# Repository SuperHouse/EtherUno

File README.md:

SuperHouse EtherUNO
===================

The EtherUNO is a 100% Arduino Compatible Board, based on the Arduino
UNO reference design, but with improvements and updates for ease of use,
cost, and getting started. It also includes on-board Ethernet with PoE
(Power-over-Ethernet) support and uses a USB-C socket.

Features:

 * LEDs visible on the edge
 * USB-C Connector
 * I2C MAC address ROM
 * Overlay guide where you need it (both top and bottom)
 * D13 pin works for everything
 * RX pin biased
 * Mounting holes

More information is available at:

  https://www.superhouse.tv/eu

Hardware
--------
The "Hardware" directory contains the PCB design as an EAGLE project.
EAGLE PCB design software is available from Autodesk free for
non-commercial use.

Credits
-------
 * Jonathan Oxer <jon@oxer.com.au>

 The EtherUNO is based on the EtherTen, which was designed by Jonathan
 Oxer and Marc Alexander.

License
-------
Copyright 2020 SuperHouse Automation Pty Ltd  www.superhouse.tv  

The hardware portion of this project is licensed under the TAPR Open
Hardware License (www.tapr.org/OHL). The "license" folder within this
repository contains a copy of this license in plain text format.

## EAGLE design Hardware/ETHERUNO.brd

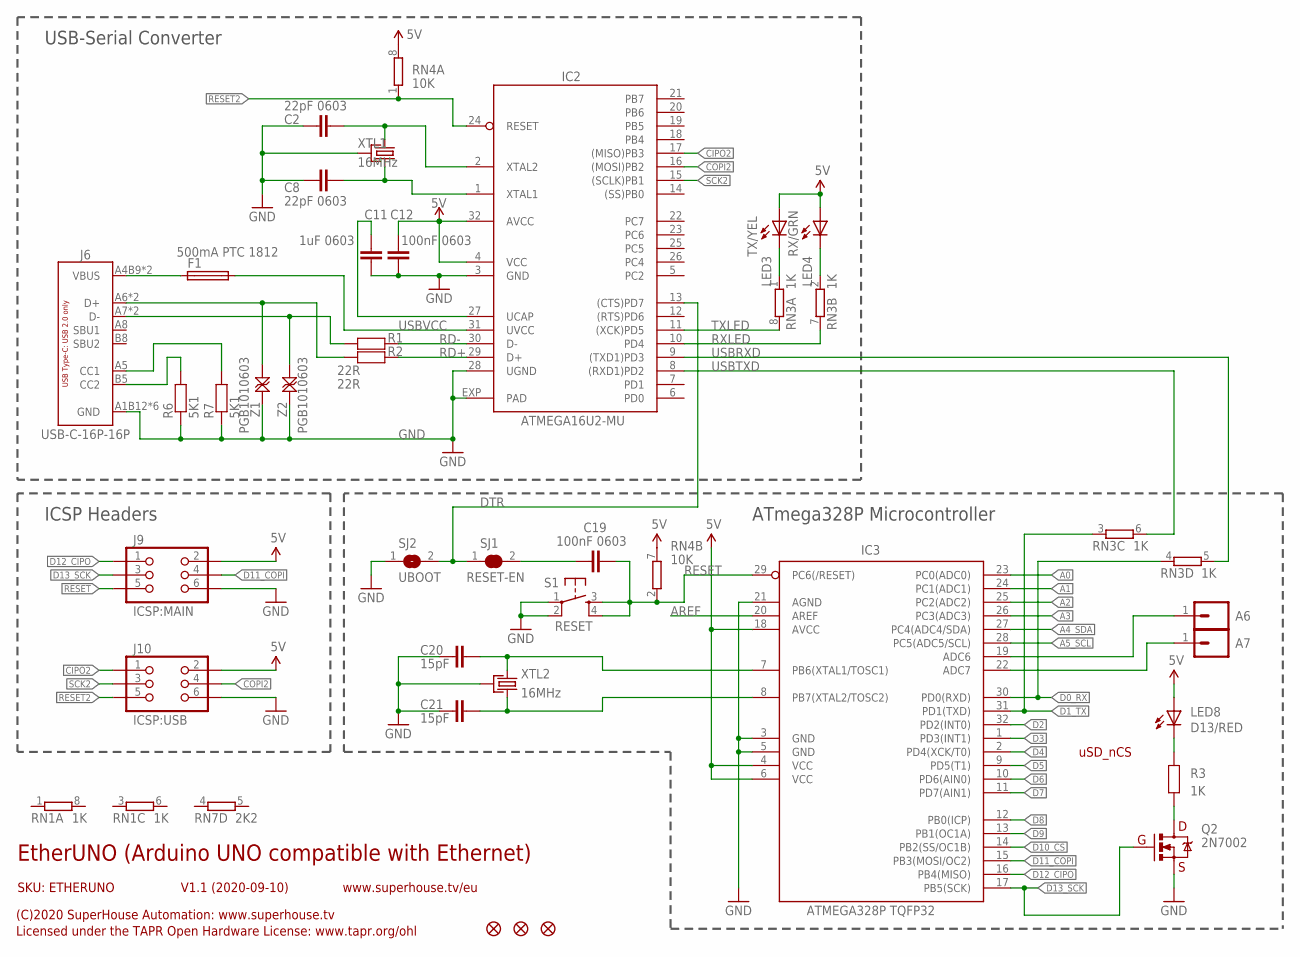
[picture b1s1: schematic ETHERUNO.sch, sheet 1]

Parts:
A6: A6; 1X01
A7: A7; 1X01
C2, C8: 22pF 0603; C0603
C11: 1uF 0603; C0603
C12, C19: 100nF 0603; C0603
C20, C21: 15pF; C0603
F1: 500mA PTC 1812; 1812
FID1, FID2, FID3: FIDUCIAL1X2.5; FIDUCIAL-1X2.5
IC2: ATMEGA16U2-MU; ATMEL_QFN32
IC3: ATMEGA328P TQFP32; TQFP32-08
J6: USB-C-16P-16P; USB-C-16P
J9: ICSP:MAIN; 2X03-ICSP
J10: ICSP:USB; 2X03-ICSP
LED3: TX/YEL; LED-0603
LED4: RX/GRN; LED-0603
LED8: D13/RED; LED-0603
Q2: 2N7002; SOT23-3
R1, R2: 22R; R0603
R3: 1K; R0603
R6, R7: 5K1; R0603
RN1, RN3: 1K; CAY16
RN4: 10K; CAY16
RN7: 2K2; CAY16
S1: RESET; TACTILE_SMT-6MM
SJ1: RESET-EN; SJC
SJ2: UBOOT; SJ
XTL1, XTL2: 16MHz; CRYSTAL-SMD-3X2
Z1, Z2: PGB1010603; TVS0603

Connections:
5V: C12.1, IC2.4 (VCC), IC2.32 (AVCC), IC3.4 (VCC), IC3.6 (VCC), IC3.18 (AVCC), J9.2, J10.2, LED3.A, LED4.A, LED8.A, RN4.7 (2), RN4.8 (2); also elsewhere on the board
A0: IC3.23 (PC0(ADC0)); also elsewhere on the board
A1: IC3.24 (PC1(ADC1)); also elsewhere on the board
A2: IC3.25 (PC2(ADC2)); also elsewhere on the board
A3: IC3.26 (PC3(ADC3)); also elsewhere on the board
A4_SDA: IC3.27 (PC4(ADC4/SDA)); also elsewhere on the board
A5_SCL: IC3.28 (PC5(ADC5/SCL)); also elsewhere on the board
AREF: IC3.20 (AREF); also elsewhere on the board
CIPO2: IC2.17 ((MISO)PB3), J10.1
COPI2: IC2.16 ((MOSI)PB2), J10.4
D0_RX: IC3.30 (PD0(RXD)), RN3.4 (1); also elsewhere on the board
D1_TX: IC3.31 (PD1(TXD)), RN3.3 (1); also elsewhere on the board
D2: IC3.32 (PD2(INT0)); also elsewhere on the board
D3: IC3.1 (PD3(INT1)); also elsewhere on the board
D4: IC3.2 (PD4(XCK/T0)); also elsewhere on the board
D5: IC3.9 (PD5(T1)); also elsewhere on the board
D6: IC3.10 (PD6(AIN0)); also elsewhere on the board
D7: IC3.11 (PD7(AIN1)); also elsewhere on the board
D8: IC3.12 (PB0(ICP)); also elsewhere on the board
D9: IC3.13 (PB1(OC1A)); also elsewhere on the board
D10_CS: IC3.14 (PB2(SS/OC1B)); also elsewhere on the board
D11_COPI: IC3.15 (PB3(MOSI/OC2)), J9.4; also elsewhere on the board
D12_CIPO: IC3.16 (PB4(MISO)), J9.1; also elsewhere on the board
D13_SCK: IC3.17 (PB5(SCK)), J9.3, Q2.1 (G); also elsewhere on the board
DTR: IC2.13 ((CTS)PD7), SJ1.1, SJ2.2
GND: C2.1, C8.1, C11.2, C12.2, C20.1, C21.1, IC2.3 (GND), IC2.28 (UGND), IC2.EXP (PAD), IC3.3 (GND), IC3.5 (GND), IC3.21 (AGND), J6.A1B12 (GND), J6.A12B1 (GND), J6.FIX1 (GND), J6.FIX2 (GND), J6.FIX3 (GND), J6.FIX4 (GND), J9.6, J10.6, Q2.2 (S), R6.1, R7.1, S1.1, S1.2, SJ2.1, XTL1.2 (GND), XTL1.4 (GND), XTL2.2 (GND), XTL2.4 (GND), Z1.2, Z2.2; also elsewhere on the board
unnamed: C20.2, IC3.7 (PB6(XTAL1/TOSC1)), XTL2.1
unnamed: C19.1, SJ1.2
unnamed: LED8.C, R3.2
unnamed: Q2.3 (D), R3.1
unnamed: C21.2, IC3.8 (PB7(XTAL2/TOSC2)), XTL2.3 (2)
unnamed: C8.2, IC2.1 (XTAL1), XTL1.3 (2)
unnamed: J6.B5 (CC2), R6.2
unnamed: LED4.C, RN3.2 (1)
unnamed: LED3.C, RN3.1
unnamed: J6.A6 (D+), J6.B6 (D+), R2.2, Z1.1
unnamed: J6.A7 (D-), J6.B7 (D-), R1.2, Z2.1
unnamed: A7.1, IC3.22 (ADC7)
unnamed: A6.1, IC3.19 (ADC6)
unnamed: J6.A5 (CC1), R7.2
unnamed: C2.2, IC2.2 (XTAL2), XTL1.1
unnamed: F1.1, J6.A4B9 (VBUS), J6.A9B4 (VBUS)
unnamed: C11.1, IC2.27 (UCAP)
RD+: IC2.29 (D+), R2.1
RD-: IC2.30 (D-), R1.1
RESET: C19.2, IC3.29 (PC6(/RESET)), J9.5, RN4.2 (1), S1.3, S1.4; also elsewhere on the board
RESET2: IC2.24 (RESET), J10.5, RN4.1
RXLED: IC2.10 (PD4), RN3.7 (2)
SCK2: IC2.15 ((SCLK)PB1), J10.3
TXLED: IC2.11 ((XCK)PD5), RN3.8 (2)
USBRXD: IC2.9 ((TXD1)PD3), RN3.5 (2)
USBTXD: IC2.8 ((RXD1)PD2), RN3.6 (2)
USBVCC: F1.2, IC2.31 (UVCC); also elsewhere on the board

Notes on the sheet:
uSD_nCS
EtherUNO (Arduino UNO compatible with Ethernet)
SKU: ETHERUNO
(C)2020 SuperHouse Automation: www.superhouse.tv
Licensed under the TAPR Open Hardware License: www.tapr.org/ohl
www.superhouse.tv/eu
V1.1 (2020-09-10)
ICSP Headers
USB-Serial Converter
ATmega328P Microcontroller

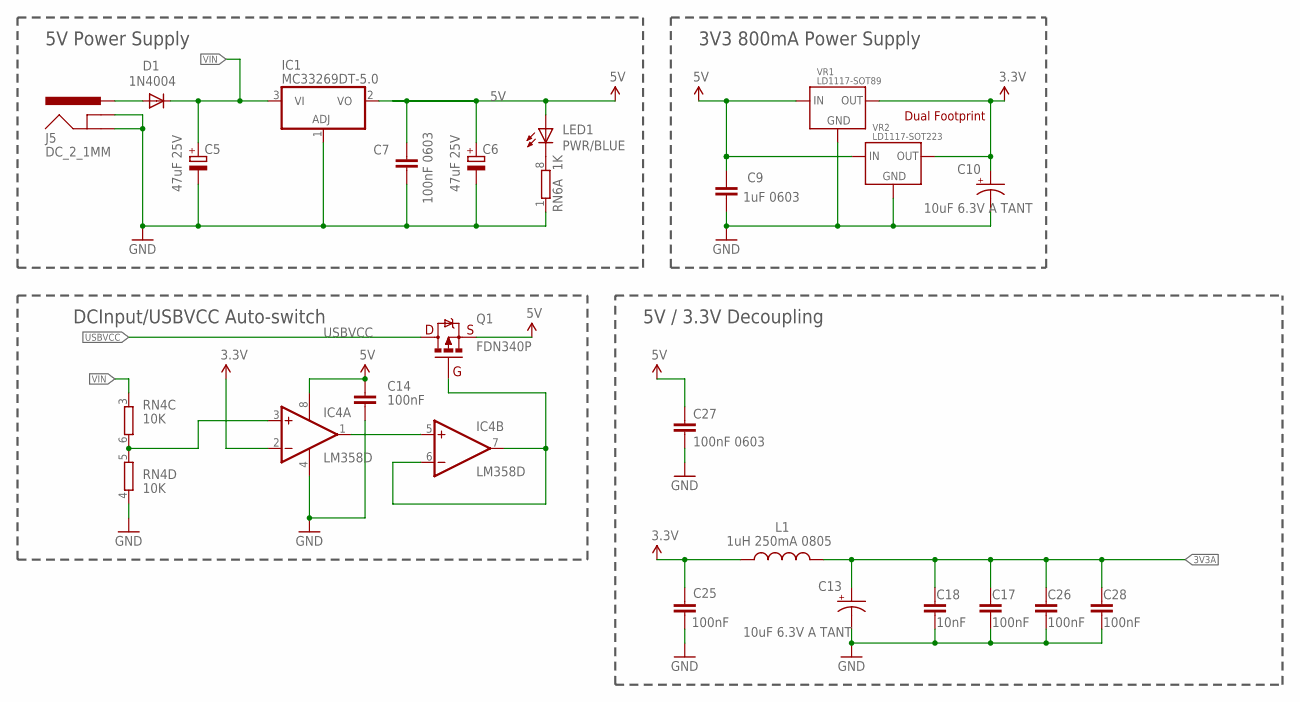
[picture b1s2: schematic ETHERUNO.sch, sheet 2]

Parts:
C5, C6: 47uF 25V; PANASONIC_D
C7, C27: 100nF 0603; C0603
C9: 1uF 0603; C0603
C10, C13: 10uF 6.3V A TANT; EIA3216
C14, C17, C25, C26, C28: 100nF; C0603
C18: 10nF; C0603
D1: 1N4004; SMA-DIODE
IC1: MC33269DT-5.0; DPACK
IC4: LM358D; SO08
J5: DC_2_1MM; POWER_JACK_SLOTS
L1: 1uH 250mA 0805; L2012C
LED1: PWR/BLUE; LED-0603
Q1: FDN340P; SOT23
RN4: 10K; CAY16
RN6: 1K; CAY16
VR1: LD1117-SOT89; SOT89
VR2: LD1117-SOT223; SOT-223

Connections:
3.3V: C10.A (+), C25.1, IC4.2 (-IN), L1.1, VR1.2 (OUT), VR1.4 (OUT), VR2.2 (OUT), VR2.4 (OUT); also elsewhere on the board
3V3A: C13.A (+), C17.1, C18.1, C26.1, C28.1, L1.2; also elsewhere on the board
5V: C6.+, C7.1, C9.1, C14.1, C27.1, IC1.2 (VO), IC4.8 (V+), LED1.A, Q1.2 (S), VR1.3 (IN), VR2.3 (IN); also elsewhere on the board
GND: C5.-, C6.-, C7.2, C9.2, C10.C (-), C13.C (-), C14.2, C17.2, C18.2, C25.2, C26.2, C27.2, C28.2, IC1.1 (ADJ), IC4.4 (V-), J5.GND, J5.GNDBREAK, RN4.4 (1), RN6.1, VR1.1 (GND), VR2.1 (GND); also elsewhere on the board
unnamed: IC4.3 (+IN), RN4.5 (2), RN4.6 (2)
unnamed: LED1.C, RN6.8 (2)
unnamed: IC4.6 (-IN), IC4.7 (OUT), Q1.1 (G)
unnamed: IC4.1 (OUT), IC4.5 (+IN)
unnamed: D1.A, J5.PWR
USBVCC: Q1.3 (D); also elsewhere on the board
VIN: C5.+, D1.C, IC1.3 (VI), RN4.3 (1); also elsewhere on the board

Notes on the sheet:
3V3 800mA Power Supply
Dual Footprint
5V Power Supply
DCInput/USBVCC Auto-switch
5V / 3.3V Decoupling

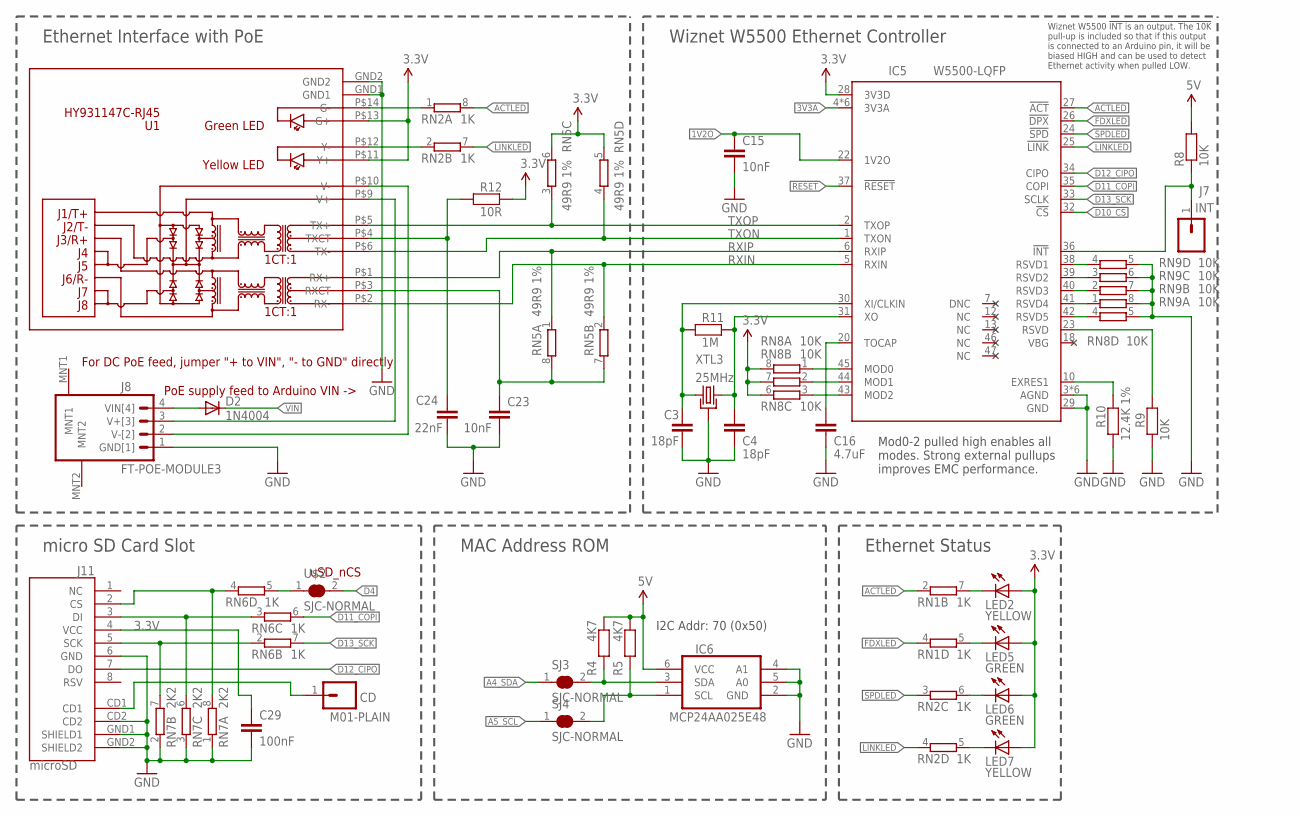
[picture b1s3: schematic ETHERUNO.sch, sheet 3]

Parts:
C3, C4: 18pF; C0603
C15, C23: 10nF; C0603
C16: 4.7uF; C0603
C24: 22nF; C0603
C29: 100nF; C0603
CD: M01-PLAIN; 1X01
D2: 1N4004; SMA-DIODE
IC5: W5500-LQFP; LQFP48
IC6: MCP24AA025E48; SOT23-6
J7: INT; 1X01
J8: FT-POE-MODULE3; FT-POE-MODULE-NOLABEL
J11: microSD; MICRO-SD-SOCKET-PP
LED2, LED7: YELLOW; LED-0603
LED5, LED6: GREEN; LED-0603
R4, R5: 4K7; R0603
R8, R9: 10K; R0603
R10: 12.4K 1%; R0603
R11: 1M; R0603
R12: 10R; R0603
RN1, RN2, RN6: 1K; CAY16
RN5: 49R9 1%; CAY16
RN7: 2K2; CAY16
RN8, RN9: 10K; CAY16
SJ3, SJ4: SJC-NORMAL; SJC
U1: HY931147C-RJ45; HY931147C
U$2: SJC-NORMAL; SJC
XTL3: 25MHz; CRYSTAL-SMD-3X2

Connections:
1V2O: C15.1, IC5.22 (1V2O)
3.3V: C29.1, IC5.28 (3V3D), J11.4 (VCC), LED2.A, LED5.A, LED6.A, LED7.A, R12.1, RN5.5 (2), RN5.6 (2), RN8.6 (2), RN8.7 (2), RN8.8 (2), U1.P$11 (Y+), U1.P$13 (G+); also elsewhere on the board
3V3A: IC5.4 (3V3A), IC5.8 (3V3A), IC5.11 (3V3A), IC5.15 (3V3A), IC5.17 (3V3A), IC5.21 (3V3A); also elsewhere on the board
5V: IC6.6 (VCC), R4.1, R5.1, R8.2; also elsewhere on the board
A4_SDA: SJ3.1; also elsewhere on the board
A5_SCL: SJ4.1; also elsewhere on the board
ACTLED: IC5.27 (!ACT), RN1.2 (1), RN2.8 (2)
D4: U$2.2; also elsewhere on the board
D10_CS: IC5.32 (!CS); also elsewhere on the board
D11_COPI: IC5.35 (COPI), RN6.6 (2); also elsewhere on the board
D12_CIPO: IC5.34 (CIPO), J11.7 (DO); also elsewhere on the board
D13_SCK: IC5.33 (SCLK), RN6.7 (2); also elsewhere on the board
FDXLED: IC5.26 (!DPX), RN1.4 (1)
GND: C3.2, C4.2, C15.2, C16.2, C23.2, C24.2, C29.2, IC5.3 (AGND), IC5.9 (AGND), IC5.14 (AGND), IC5.16 (AGND), IC5.19 (AGND), IC5.29 (GND), IC5.48 (AGND), IC6.2 (GND), IC6.4 (A1), IC6.5 (A0), J8.1 (GND[1]), J11.6 (GND), J11.CD2, J11.GND1 (SHIELD1), J11.GND2 (SHIELD2), R9.2, R10.2, RN7.1, RN7.2 (1), RN7.3 (1), RN8.5 (2), RN9.5 (2), RN9.6 (2), RN9.7 (2), RN9.8 (2), U1.GND1, U1.GND2, XTL3.2 (GND), XTL3.4 (GND); also elsewhere on the board
LINKLED: IC5.25 (!LINK), RN2.4 (1), RN2.7 (2)
unnamed: C23.1, RN5.7 (2), RN5.8 (2), U1.P$3 (RXCT)
unnamed: IC6.1 (SCL), R5.2, SJ4.2
unnamed: C4.1, IC5.31 (XO), R11.1, XTL3.3 (2)
unnamed: D2.A, J8.4 (VIN[4])
unnamed: J11.2 (CS), RN6.4 (1), RN7.8 (2)
unnamed: CD.1, J11.CD1
unnamed: J11.5 (SCK), RN6.2 (1), RN7.7 (2)
unnamed: J11.3 (DI), RN6.3 (1), RN7.6 (2)
unnamed: LED6.C, RN2.6 (2)
unnamed: C3.1, IC5.30 (XI/CLKIN), R11.2, XTL3.1
unnamed: LED7.C, RN2.5 (2)
unnamed: IC6.3 (SDA), R4.2, SJ3.2
unnamed: C16.1, IC5.20 (TOCAP)
unnamed: C24.1, R12.2, U1.P$4 (TXCT)
unnamed: IC5.10 (EXRES1), R10.1
unnamed: IC5.23 (RSVD), R9.1
unnamed: IC5.36 (!INT), J7.1, R8.1
unnamed: IC5.45 (MOD0), RN8.1
unnamed: IC5.44 (MOD1), RN8.2 (1)
unnamed: IC5.43 (MOD2), RN8.3 (1)
unnamed: IC5.42 (RSVD5), RN8.4 (1)
unnamed: IC5.41 (RSVD4), RN9.1
unnamed: IC5.40 (RSVD3), RN9.2 (1)
unnamed: IC5.39 (RSVD2), RN9.3 (1)
unnamed: IC5.38 (RSVD1), RN9.4 (1)
unnamed: RN6.5 (2), U$2.1
unnamed: RN2.1, U1.P$14 (G-)
unnamed: J8.3 (V+[3]), U1.P$9 (V+)
unnamed: J8.2 (V-[2]), U1.P$10 (V-)
unnamed: LED5.C, RN1.5 (2)
unnamed: LED2.C, RN1.7 (2)
unnamed: RN2.2 (1), U1.P$12 (Y-)
RESET: IC5.37 (!RESET); also elsewhere on the board
RXIN: IC5.5 (RXIN), RN5.2 (1), U1.P$2 (RX-)
RXIP: IC5.6 (RXIP), RN5.1, U1.P$1 (RX+)
SPDLED: IC5.24 (!SPD), RN2.3 (1)
TXON: IC5.1 (TXON), RN5.4 (1), U1.P$6 (TX-)
TXOP: IC5.2 (TXOP), RN5.3 (1), U1.P$5 (TX+)
VIN: D2.C; also elsewhere on the board

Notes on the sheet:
uSD_nCS
micro SD Card Slot
I2C Addr: 70 (0x50)
Ethernet Status
PoE supply feed to Arduino VIN ->
For DC PoE feed, jumper "+ to VIN", "- to GND" directly
Ethernet Interface with PoE
MAC Address ROM
Wiznet W5500 Ethernet Controller
Mod0-2 pulled high enables all modes. Strong external pullups improves EMC performance.
Wiznet W5500 !INT is an output. The 10K pull-up is included so that if this output is connected to an Arduino pin, it will be biased HIGH and can be used to detect Ethernet activity when pulled LOW.

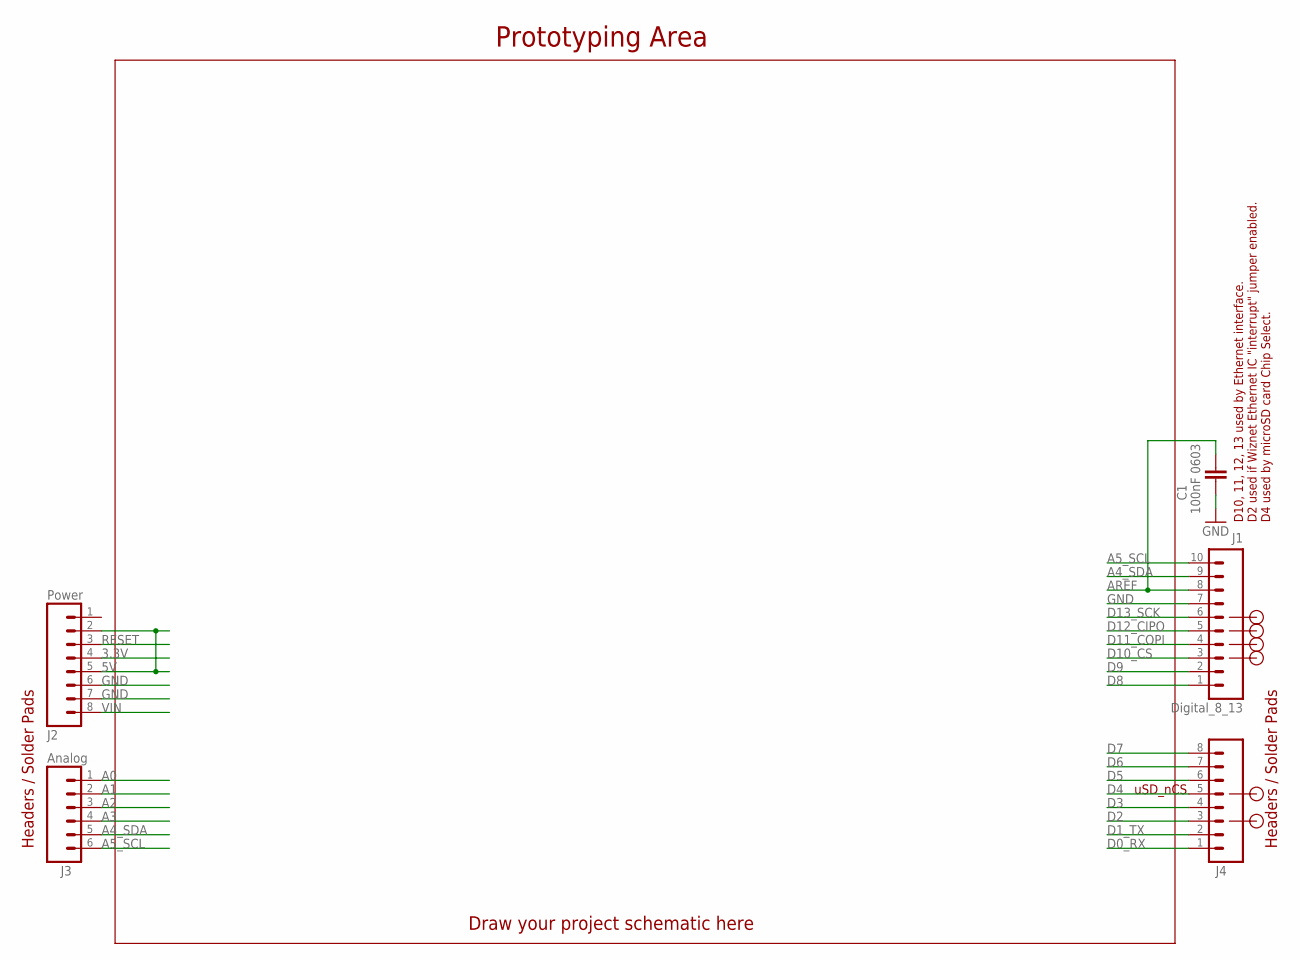
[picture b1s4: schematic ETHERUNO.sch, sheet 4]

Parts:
C1: 100nF 0603; C0603
J1: Digital_8_13; 1X10-S
J2: Power; 1X08-S
J3: Analog; 1X06-S
J4: Digital_0_7; 1X08-S

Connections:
3.3V: J2.4; also elsewhere on the board
5V: J2.2, J2.5; also elsewhere on the board
A0: J3.1; also elsewhere on the board
A1: J3.2; also elsewhere on the board
A2: J3.3; also elsewhere on the board
A3: J3.4; also elsewhere on the board
A4_SDA: J1.9, J3.5; also elsewhere on the board
A5_SCL: J1.10, J3.6; also elsewhere on the board
AREF: C1.1, J1.8; also elsewhere on the board
D0_RX: J4.1; also elsewhere on the board
D1_TX: J4.2; also elsewhere on the board
D2: J4.3; also elsewhere on the board
D3: J4.4; also elsewhere on the board
D4: J4.5; also elsewhere on the board
D5: J4.6; also elsewhere on the board
D6: J4.7; also elsewhere on the board
D7: J4.8; also elsewhere on the board
D8: J1.1; also elsewhere on the board
D9: J1.2; also elsewhere on the board
D10_CS: J1.3; also elsewhere on the board
D11_COPI: J1.4; also elsewhere on the board
D12_CIPO: J1.5; also elsewhere on the board
D13_SCK: J1.6; also elsewhere on the board
GND: C1.2, J1.7, J2.6, J2.7; also elsewhere on the board
RESET: J2.3; also elsewhere on the board
VIN: J2.8; also elsewhere on the board

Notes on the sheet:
Prototyping Area
Headers / Solder Pads
Draw your project schematic here
D10, 11, 12, 13 used by Ethernet interface.
D2 used if Wiznet Ethernet IC "interrupt" jumper enabled.
uSD_nCS
D4 used by microSD card Chip Select.

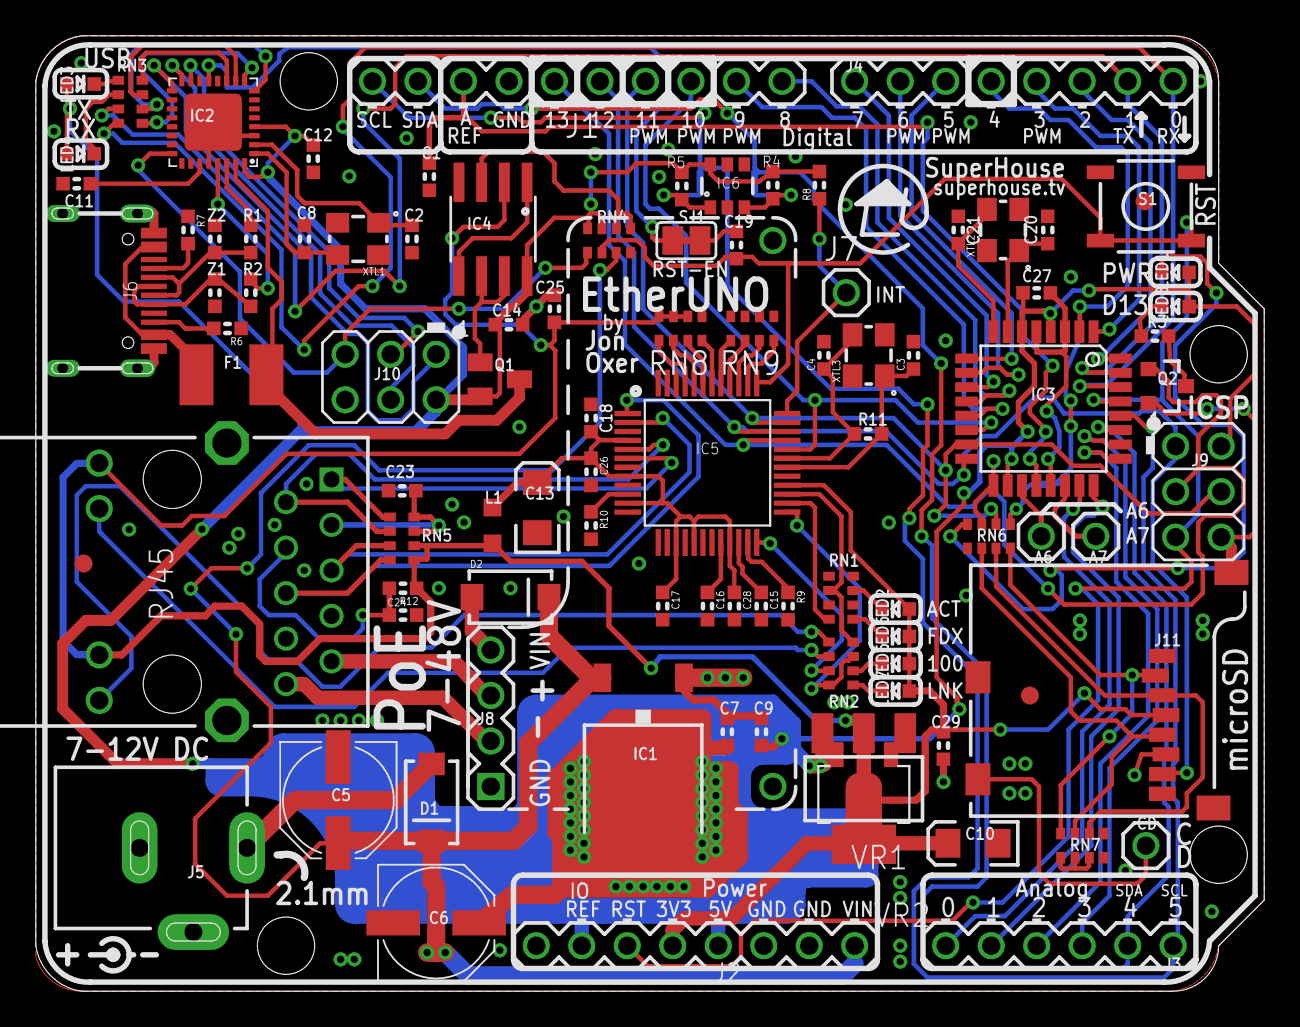
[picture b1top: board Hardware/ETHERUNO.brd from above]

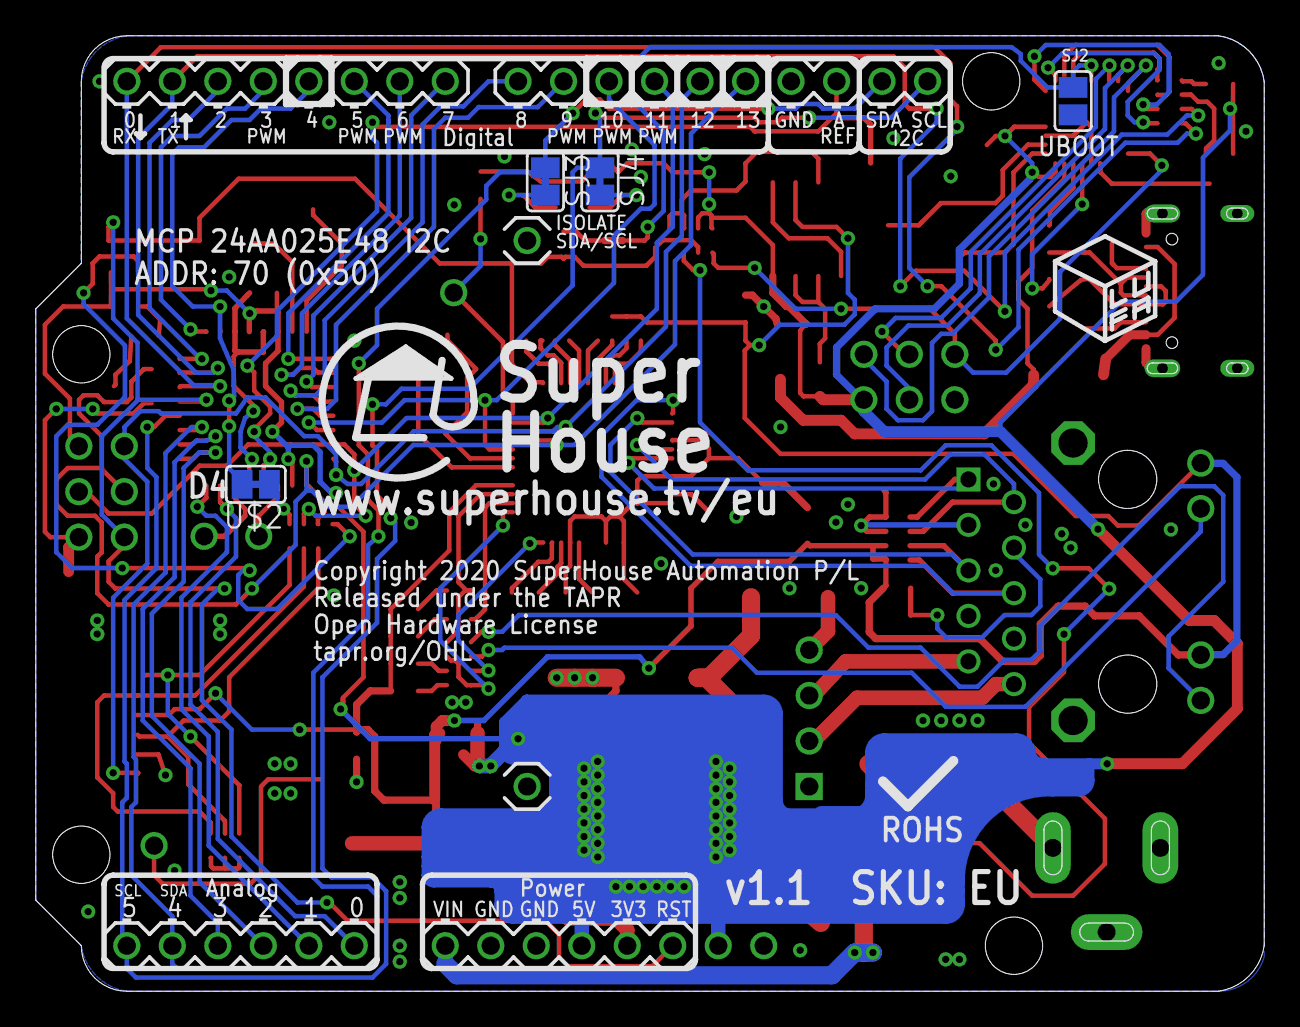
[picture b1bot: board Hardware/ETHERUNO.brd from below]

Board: 2 copper layers, 68.6 x 53.3 mm, 100 parts (4 on the bottom side), 102 nets.

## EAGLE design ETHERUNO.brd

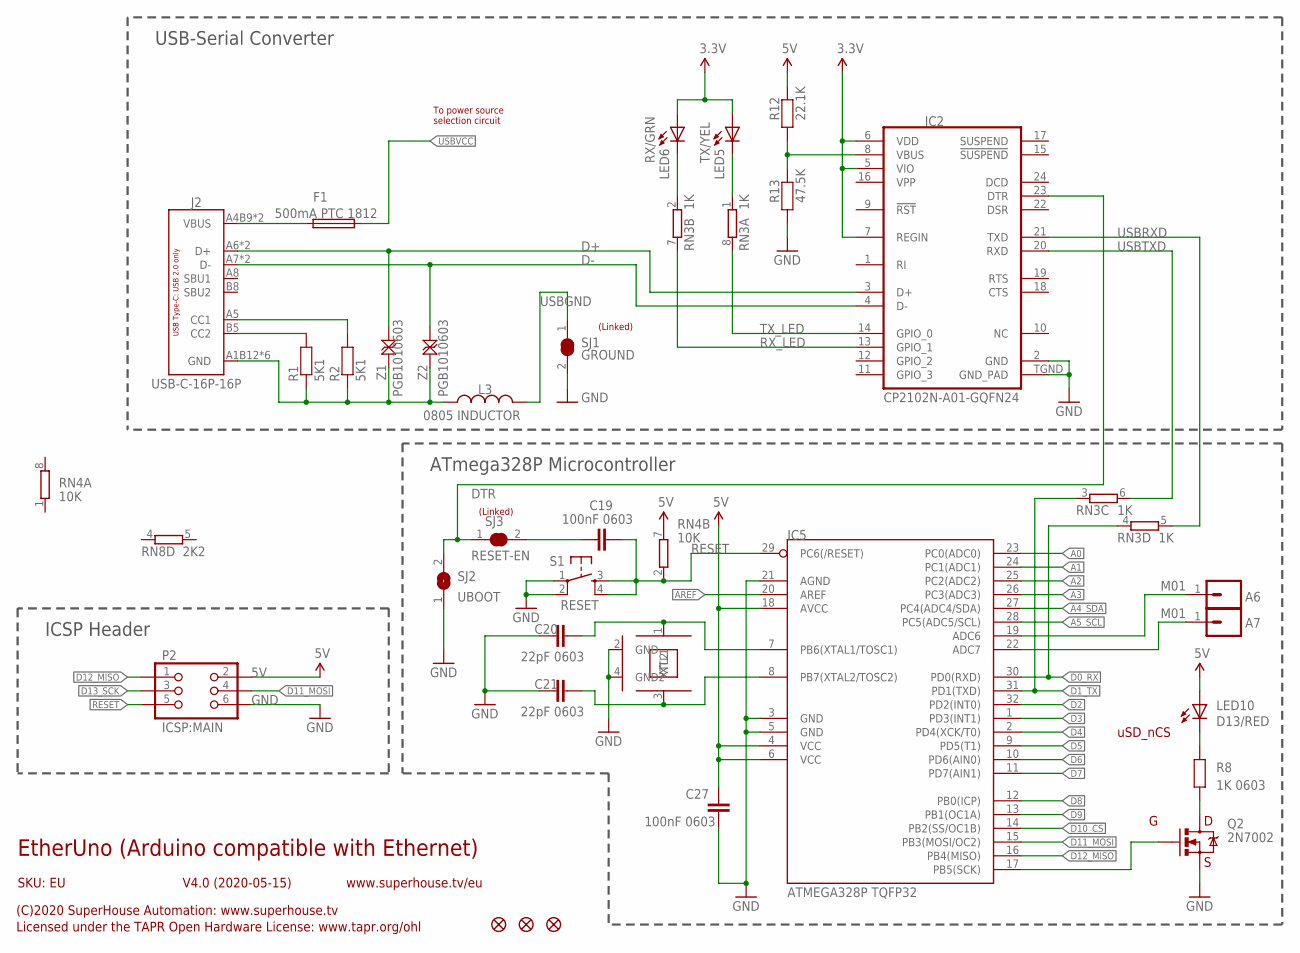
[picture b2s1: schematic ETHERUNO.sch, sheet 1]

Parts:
A6, A7: M01; 1X01
C19, C27: 100nF 0603; C0603
C20, C21: 22pF 0603; C0603
F1: 500mA PTC 1812; 1812
FID1, FID2, FID3: FIDUCIAL1X2.5; FIDUCIAL-1X2.5
IC2: CP2102N-A01-GQFN24; QFN-24
IC5: ATMEGA328P TQFP32; TQFP32-08
J2: USB-C-16P-16P; USB-C-16P
L3: 0805 INDUCTOR; 0805-LARGE
LED5: TX/YEL; LED-0603
LED6: RX/GRN; LED-0603
LED10: D13/RED; LED-0603
P2: ICSP:MAIN; 2X03-ICSP
Q2: 2N7002; SOT23-3
R1, R2: 5K1; R0603
R8: 1K 0603; R0603
R12: 22.1K; R0603
R13: 47.5K; R0603
RN3: 1K; CAY16
RN4: 10K; CAY16
RN8: 2K2; CAY16
S1: RESET; TACTILE_SMT-6MM
SJ1: GROUND; SJC
SJ2: UBOOT; SJ
SJ3: RESET-EN; SJC
U$19: CRYSTAL-GND3X2; CRYSTAL-SMD-3X2
Z1, Z2: PGB1010603; TVS0603

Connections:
3.3V: IC2.5 (VIO), IC2.6 (VDD), IC2.7 (REGIN), LED5.A, LED6.A; also elsewhere on the board
5V: C27.1, IC5.4 (VCC), IC5.6 (VCC), IC5.18 (AVCC), LED10.A, P2.2, R12.2, RN4.7 (2); also elsewhere on the board
A0: IC5.23 (PC0(ADC0)); also elsewhere on the board
A1: IC5.24 (PC1(ADC1)); also elsewhere on the board
A2: IC5.25 (PC2(ADC2)); also elsewhere on the board
A3: IC5.26 (PC3(ADC3)); also elsewhere on the board
A4_SDA: IC5.27 (PC4(ADC4/SDA)); also elsewhere on the board
A5_SCL: IC5.28 (PC5(ADC5/SCL)); also elsewhere on the board
AREF: IC5.20 (AREF); also elsewhere on the board
D0_RX: IC5.30 (PD0(RXD)), RN3.4 (1); also elsewhere on the board
D1_TX: IC5.31 (PD1(TXD)), RN3.3 (1); also elsewhere on the board
D2: IC5.32 (PD2(INT0)); also elsewhere on the board
D3: IC5.1 (PD3(INT1)); also elsewhere on the board
D4: IC5.2 (PD4(XCK/T0)); also elsewhere on the board
D5: IC5.9 (PD5(T1)); also elsewhere on the board
D6: IC5.10 (PD6(AIN0)); also elsewhere on the board
D7: IC5.11 (PD7(AIN1)); also elsewhere on the board
D8: IC5.12 (PB0(ICP)); also elsewhere on the board
D9: IC5.13 (PB1(OC1A)); also elsewhere on the board
D10_CS: IC5.14 (PB2(SS/OC1B)); also elsewhere on the board
D11_MOSI: IC5.15 (PB3(MOSI/OC2)), P2.4; also elsewhere on the board
D12_MISO: IC5.16 (PB4(MISO)), P2.1; also elsewhere on the board
D13_SCK: IC5.17 (PB5(SCK)), P2.3, Q2.1 (G); also elsewhere on the board
D+: IC2.3 (D+), J2.A6 (D+), J2.B6 (D+), Z1.1
D-: IC2.4 (D-), J2.A7 (D-), J2.B7 (D-), Z2.1
DTR: IC2.23 (DTR), SJ2.2, SJ3.1
GND: C20.1, C21.1, C27.2, IC2.2 (GND), IC2.TGND (GND_PAD), IC5.3 (GND), IC5.5 (GND), IC5.21 (AGND), P2.6, Q2.2 (S), R13.1, S1.1, S1.2, SJ1.2, SJ2.1, U$19.2 (GND), U$19.4 (GND2); also elsewhere on the board
unnamed: C20.2, IC5.7 (PB6(XTAL1/TOSC1)), U$19.1 (XTL1)
unnamed: C19.1, SJ3.2
unnamed: LED10.C, R8.2
unnamed: Q2.3 (D), R8.1
unnamed: C21.2, IC5.8 (PB7(XTAL2/TOSC2)), U$19.3 (XTL2)
unnamed: J2.A1B12 (GND), J2.A12B1 (GND), J2.FIX1 (GND), J2.FIX2 (GND), J2.FIX3 (GND), J2.FIX4 (GND), L3.1, R1.1, R2.1, Z1.2, Z2.2
unnamed: J2.B5 (CC2), R1.2
unnamed: LED6.C, RN3.2 (1)
unnamed: LED5.C, RN3.1
unnamed: A7.1, IC5.22 (ADC7)
unnamed: A6.1, IC5.19 (ADC6)
unnamed: J2.A5 (CC1), R2.2
unnamed: IC2.8 (VBUS), R12.1, R13.2
unnamed: F1.1, J2.A4B9 (VBUS), J2.A9B4 (VBUS)
RESET: C19.2, IC5.29 (PC6(/RESET)), P2.5, RN4.2 (1), S1.3, S1.4; also elsewhere on the board
RX_LED: IC2.13 (GPIO_1), RN3.7 (2)
TX_LED: IC2.14 (GPIO_0), RN3.8 (2)
USBGND: L3.2, SJ1.1
USBRXD: IC2.21 (TXD), RN3.5 (2)
USBTXD: IC2.20 (RXD), RN3.6 (2)
USBVCC: F1.2; also elsewhere on the board

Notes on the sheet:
uSD_nCS
(Linked)
EtherUno (Arduino compatible with Ethernet)
SKU: EU
(C)2020 SuperHouse Automation: www.superhouse.tv
Licensed under the TAPR Open Hardware License: www.tapr.org/ohl
www.superhouse.tv/eu
V4.0 (2020-05-15)
USB-Serial Converter
ATmega328P Microcontroller
ICSP Header
To power source selection circuit

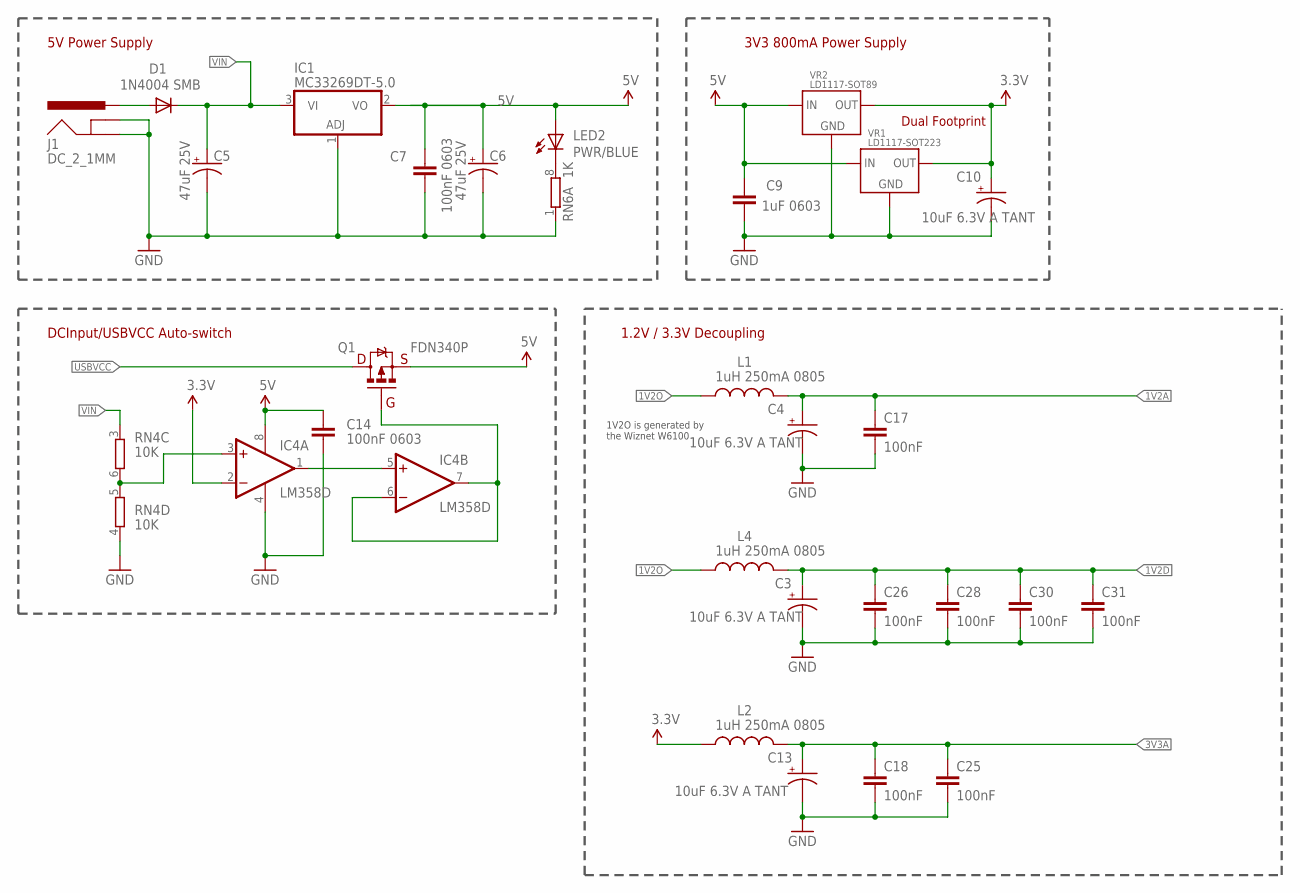
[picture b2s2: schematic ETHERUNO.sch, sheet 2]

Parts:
C3, C4, C10, C13: 10uF 6.3V A TANT; EIA3216
C5, C6: 47uF 25V; PANASONIC_D
C7, C14: 100nF 0603; C0603
C9: 1uF 0603; C0603
C17, C18, C25, C26, C28, C30, C31: 100nF; C0603
D1: 1N4004 SMB; SMA-DIODE
IC1: MC33269DT-5.0; DPACK
IC4: LM358D; SO08
J1: DC_2_1MM; POWER_JACK_SLOTS
L1, L2, L4: 1uH 250mA 0805; 0805-LARGE
LED2: PWR/BLUE; LED-0603
Q1: FDN340P; SOT23
RN4: 10K; CAY16
RN6: 1K; CAY16
VR1: LD1117-SOT223; SOT-223
VR2: LD1117-SOT89; SOT89

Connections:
1V2A: C4.A (+), C17.1, L1.2; also elsewhere on the board
1V2D: C3.A (+), C26.1, C28.1, C30.1, C31.1, L4.2; also elsewhere on the board
1V2O: L1.1, L4.1; also elsewhere on the board
3.3V: C10.A (+), IC4.2 (-IN), L2.1, VR1.2 (OUT), VR1.4 (OUT), VR2.2 (OUT), VR2.4 (OUT); also elsewhere on the board
3V3A: C13.A (+), C18.1, C25.1, L2.2; also elsewhere on the board
5V: C6.+, C7.1, C9.1, C14.1, IC1.2 (VO), IC4.8 (V+), LED2.A, Q1.2 (S), VR1.3 (IN), VR2.3 (IN); also elsewhere on the board
GND: C3.C (-), C4.C (-), C5.-, C6.-, C7.2, C9.2, C10.C (-), C13.C (-), C14.2, C17.2, C18.2, C25.2, C26.2, C28.2, C30.2, C31.2, IC1.1 (ADJ), IC4.4 (V-), J1.GND, J1.GNDBREAK, RN4.4 (1), RN6.1, VR1.1 (GND), VR2.1 (GND); also elsewhere on the board
unnamed: IC4.3 (+IN), RN4.5 (2), RN4.6 (2)
unnamed: LED2.C, RN6.8 (2)
unnamed: IC4.6 (-IN), IC4.7 (OUT), Q1.1 (G)
unnamed: IC4.1 (OUT), IC4.5 (+IN)
unnamed: D1.A, J1.PWR
USBVCC: Q1.3 (D); also elsewhere on the board
VIN: C5.+, D1.C, IC1.3 (VI), RN4.3 (1); also elsewhere on the board

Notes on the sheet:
5V Power Supply
DCInput/USBVCC Auto-switch
1.2V / 3.3V Decoupling
3V3 800mA Power Supply
Dual Footprint
1V2O is generated by the Wiznet W6100

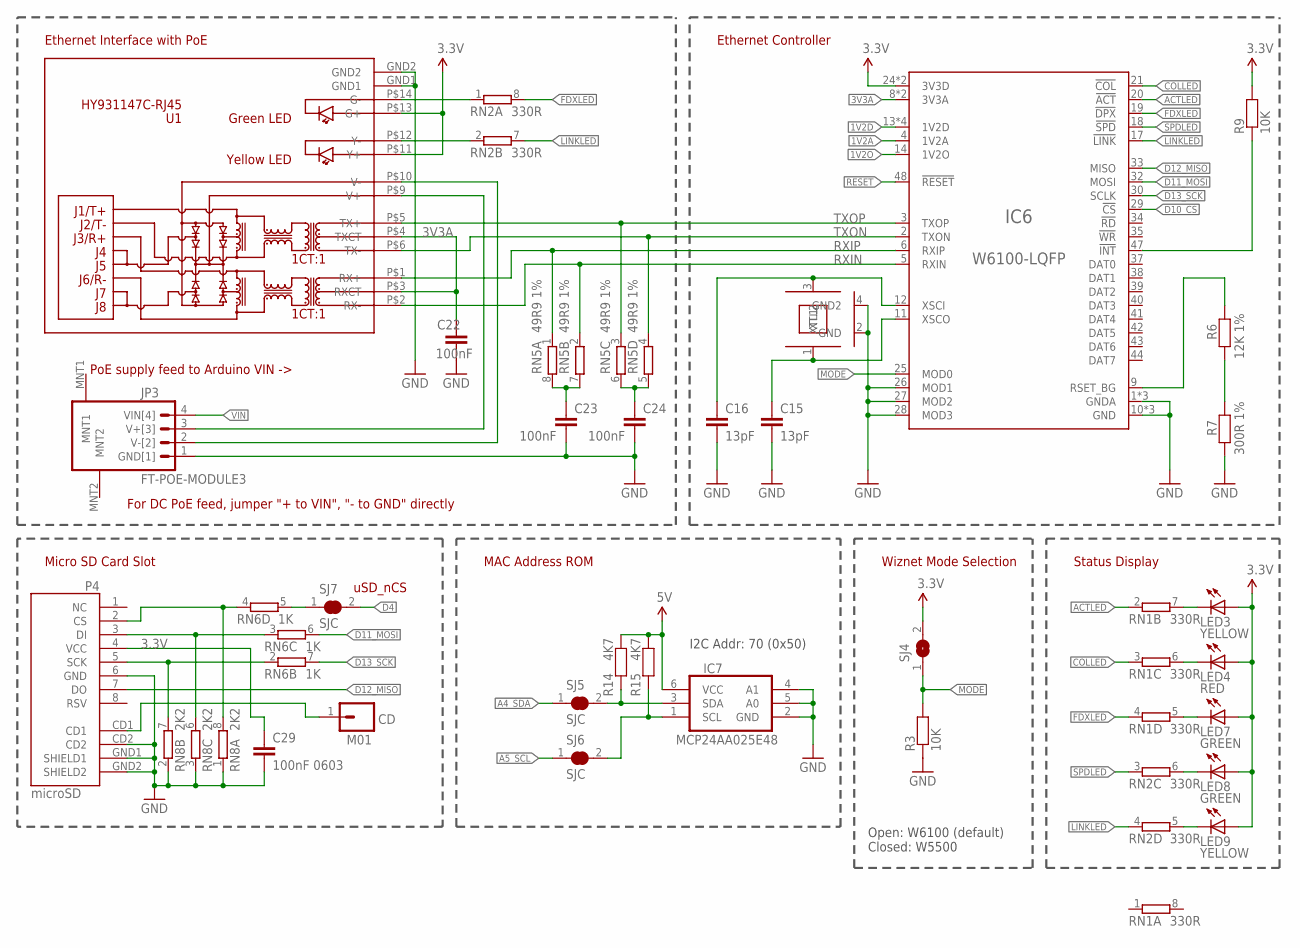
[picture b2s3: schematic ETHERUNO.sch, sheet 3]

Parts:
C15, C16: 13pF; C0603
C22, C23, C24: 100nF; C0603
C29: 100nF 0603; C0603
CD: M01; 1X01
IC6: W6100-LQFP; LQFP48
IC7: MCP24AA025E48; SOT23-6
JP3: FT-POE-MODULE3; FT-POE-MODULE-NOLABEL
LED3, LED9: YELLOW; LED-0603
LED4: RED; LED-0603
LED7, LED8: GREEN; LED-0603
P4: microSD; MICRO-SD-SOCKET-PP
R3, R9: 10K; R0603
R6: 12K 1%; R0603
R7: 300R 1%; R0603
R14, R15: 4K7; R0603
RN1, RN2: 330R; CAY16
RN5: 49R9 1%; CAY16
RN6: 1K; CAY16
RN8: 2K2; CAY16
SJ4: SJ-NORMAL; SJ
SJ5, SJ6, SJ7: SJC
U1: HY931147C-RJ45; HY931147C
U$17: CRYSTAL-GND3X2; CRYSTAL-SMD-3X2

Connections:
1V2A: IC6.4 (1V2A); also elsewhere on the board
1V2D: IC6.13 (1V2D), IC6.22 (1V2D), IC6.31 (1V2D), IC6.45 (1V2D); also elsewhere on the board
1V2O: IC6.14 (1V2O); also elsewhere on the board
3.3V: C29.1, IC6.24 (3V3D), IC6.36 (3V3D), LED3.A, LED4.A, LED7.A, LED8.A, LED9.A, P4.4 (VCC), R9.2, SJ4.2, U1.P$11 (Y+), U1.P$13 (G+); also elsewhere on the board
3V3A: C22.1, IC6.8 (3V3A), IC6.15 (3V3A), U1.P$3 (RXCT), U1.P$4 (TXCT); also elsewhere on the board
5V: IC7.6 (VCC), R14.1, R15.1; also elsewhere on the board
A4_SDA: SJ5.1; also elsewhere on the board
A5_SCL: SJ6.1; also elsewhere on the board
ACTLED: IC6.20 (!ACT), RN1.2 (1)
COLLED: IC6.21 (!COL), RN1.3 (1)
D4: SJ7.2; also elsewhere on the board
D10_CS: IC6.29 (!CS); also elsewhere on the board
D11_MOSI: IC6.32 (MOSI), RN6.6 (2); also elsewhere on the board
D12_MISO: IC6.33 (MISO), P4.7 (DO); also elsewhere on the board
D13_SCK: IC6.30 (SCLK), RN6.7 (2); also elsewhere on the board
FDXLED: IC6.19 (!DPX), RN1.4 (1), RN2.8 (2)
GND: C15.2, C16.2, C22.2, C23.2, C24.2, C29.2, IC6.1 (GNDA), IC6.7 (GNDA), IC6.10 (GND), IC6.16 (GNDA), IC6.23 (GND), IC6.26 (MOD1), IC6.27 (MOD2), IC6.28 (MOD3), IC6.46 (GND), IC7.2 (GND), IC7.4 (A1), IC7.5 (A0), JP3.1 (GND[1]), P4.6 (GND), P4.CD2, P4.GND1 (SHIELD1), P4.GND2 (SHIELD2), R3.1, R7.2, RN8.1, RN8.2 (1), RN8.3 (1), U1.GND1, U1.GND2, U$17.2 (GND), U$17.4 (GND2); also elsewhere on the board
LINKLED: IC6.17 (!LINK), RN2.4 (1), RN2.7 (2)
MODE: IC6.25 (MOD0), R3.2, SJ4.1
unnamed: C24.1, RN5.5 (2), RN5.6 (2)
unnamed: IC7.1 (SCL), R15.2, SJ6.2
unnamed: P4.2 (CS), RN6.4 (1), RN8.8 (2)
unnamed: CD.1, P4.CD1
unnamed: P4.5 (SCK), RN6.2 (1), RN8.7 (2)
unnamed: P4.3 (DI), RN6.3 (1), RN8.6 (2)
unnamed: LED8.C, RN2.6 (2)
unnamed: RN6.5 (2), SJ7.1
unnamed: LED9.C, RN2.5 (2)
unnamed: IC7.3 (SDA), R14.2, SJ5.2
unnamed: C15.1, IC6.11 (XSCO), U$17.1 (XTL1)
unnamed: C16.1, IC6.12 (XSCI), U$17.3 (XTL2)
unnamed: R6.2, R7.1
unnamed: IC6.9 (RSET_BG), R6.1
unnamed: IC6.47 (!INT), R9.1
unnamed: RN2.1, U1.P$14 (G-)
unnamed: JP3.3 (V+[3]), U1.P$9 (V+)
unnamed: JP3.2 (V-[2]), U1.P$10 (V-)
unnamed: C23.1, RN5.7 (2), RN5.8 (2)
unnamed: LED7.C, RN1.5 (2)
unnamed: LED4.C, RN1.6 (2)
unnamed: LED3.C, RN1.7 (2)
unnamed: RN2.2 (1), U1.P$12 (Y-)
RESET: IC6.48 (!RESET); also elsewhere on the board
RXIN: IC6.5 (RXIN), RN5.2 (1), U1.P$2 (RX-)
RXIP: IC6.6 (RXIP), RN5.1, U1.P$1 (RX+)
SPDLED: IC6.18 (!SPD), RN2.3 (1)
TXON: IC6.2 (TXON), RN5.4 (1), U1.P$6 (TX-)
TXOP: IC6.3 (TXOP), RN5.3 (1), U1.P$5 (TX+)
VIN: JP3.4 (VIN[4]); also elsewhere on the board

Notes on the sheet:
Status Display
PoE supply feed to Arduino VIN ->
For DC PoE feed, jumper "+ to VIN", "- to GND" directly
Ethernet Interface with PoE
Open: W6100 (default) Closed: W5500
Wiznet Mode Selection
Ethernet Controller
I2C Addr: 70 (0x50)
uSD_nCS
Micro SD Card Slot
MAC Address ROM

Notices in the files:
Hardware/ETHERUNO.brd:
Copyright 2020 SuperHouse Automation P/L
Open Hardware License
